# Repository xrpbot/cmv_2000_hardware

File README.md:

CMV2000 adapter kit
===================

This adapter kit allows connecting an [AMS CMV2000](https://ams.com/cmv2000)
image sensor to a ZedBoard (and probably other FPGA devboards) via the [FPGA
Mezzanine Card (FMC)](https://en.wikipedia.org/wiki/FPGA_Mezzanine_Card)
connector.

The CMV2000 is a high-speed image sensor intended for machine vision
applications (2 megapixels, 340 fps). While relatively expensive, it is one of
the few mid-range image sensors where reasonably complete documentation is
freely available (without NDA) from the manufacturer.

The hardware is split in two PCBs, connected by two high speed flat flex
cables. The first board contains the sensor, the second board connects to the
FMC port on the ZedBoard.

The sensor is powered by the ZedBoard, using the 12 V supply provided on the FMC
connector. Level shifters are used to translate all single-ended signals from
the FPGA I/O voltage to the 3.3 V used by the sensor.

The FMC board contains integrated 1k probes for some of the high-speed
differential signals. Additionally, a pin header allows probing the low-speed
single-ended signals.

For space reasons, the 1k probes use U.FL connectors for the connection to the
oscilloscope. The U.FL connectors have a very limited number of mating cycles
and the number of connections must therefore be kept to a minimum. Note that a
1k probe generally requires a termination (typically 50 Ω) at the oscilloscope;
with a high-impedance input, results will be very poor. If the 1k probes are
not required, the connectors and the corresponding resistors can simply be left
unpopulated.

See [pinmap.txt](pinmap.txt) for a list of connections from FPGA package pins
to camera pins.

Note that this repository uses submodules.

FMC board
---------

### Stackup

The FMC PCB is designed to be produced with 4 layers using the
[JLCPCB](https://jlcpcb.com/) JLC2313 stackup. (0.1 mm prepreg, ε<sub>r</sub> =
4.05 between the outer and inner layer.)

Using the JLCPCB impedance calculator, the following trace parameters were obtained:

100 Ω differential:
4.00 mil (102 µm) trace width / 5.00 mil (127 µm) space

50 Ω single-ended:
5.78 mil (147 µm) trace width

These results were cross-checked using Maarten Baerts [AlterPCB
TLineSim](https://www.maartenbaert.be/alterpcb/tlinesim/) tool. In addition,
the influence of ground pour on the signal layer was investigated (using the
"Coplanar Waveguide" geometry). A distance of >= 200 µm between the edge of the
signal trace and ground seems to have little effect on the impedance.

### Vias

JLC multilayer: min. via drill: 0.2 mm, min. via diameter: 0.45 mm

Known issues
------------

* Sensor board: The 3.0 V rail is generated with an LDO (U202) from the 3.3 V
rail. However, this drop is too low for the LDO to properly operate. On the
physical board, this is fixed with a bodge wire connecting the input of U202 to
the 5.0 V rail instead. However, this fix is not contained in the schematic or
layout.

* After the sensor board PCB was produced, we found out that the intended
31-pin connector (P102) was no longer available. Thus, a 41-pin connector had
to be bodged on (sacrificing the I2C EEPROM). This change is not documented in
the schematic. However, when the current version of the FMC board was designed,
it was adapted to the situation and uses a 41-pin connector. The end result is
that the boards, as found in this repository, are incompatible: the sensor
board uses a 51-pin and a 31-pin connector, while the FMC board uses a 51-pin
and a 41-pin connector.

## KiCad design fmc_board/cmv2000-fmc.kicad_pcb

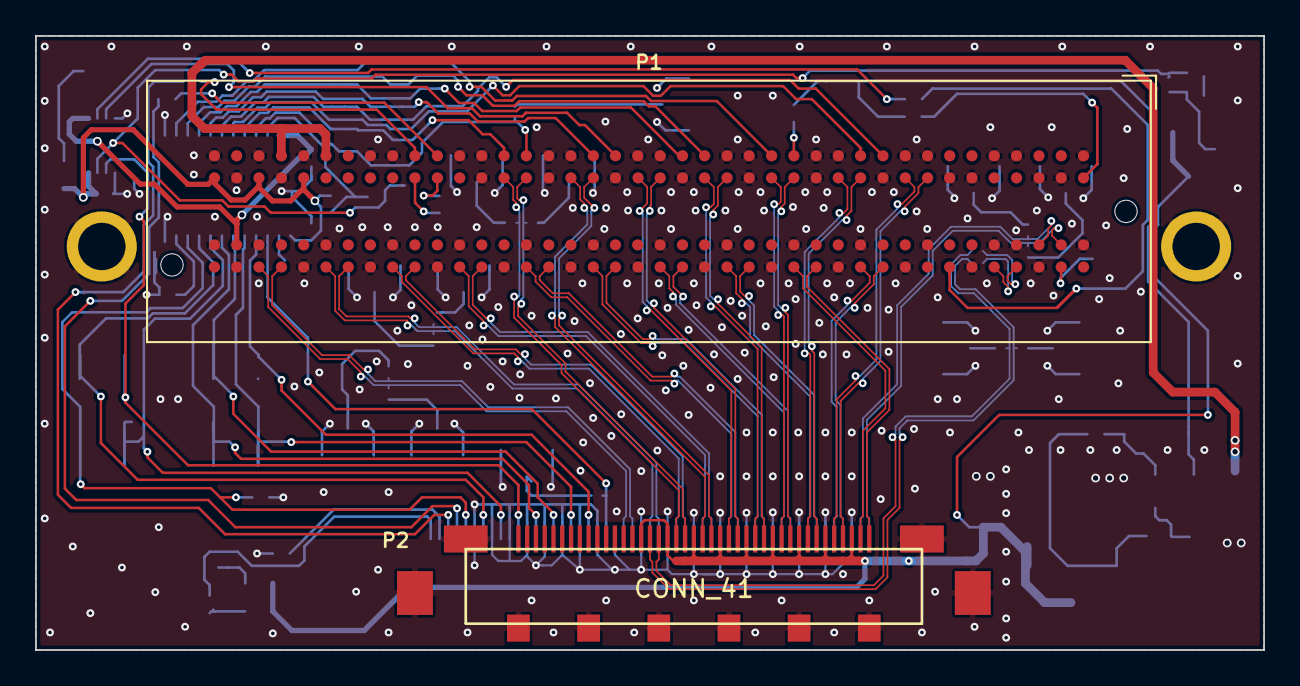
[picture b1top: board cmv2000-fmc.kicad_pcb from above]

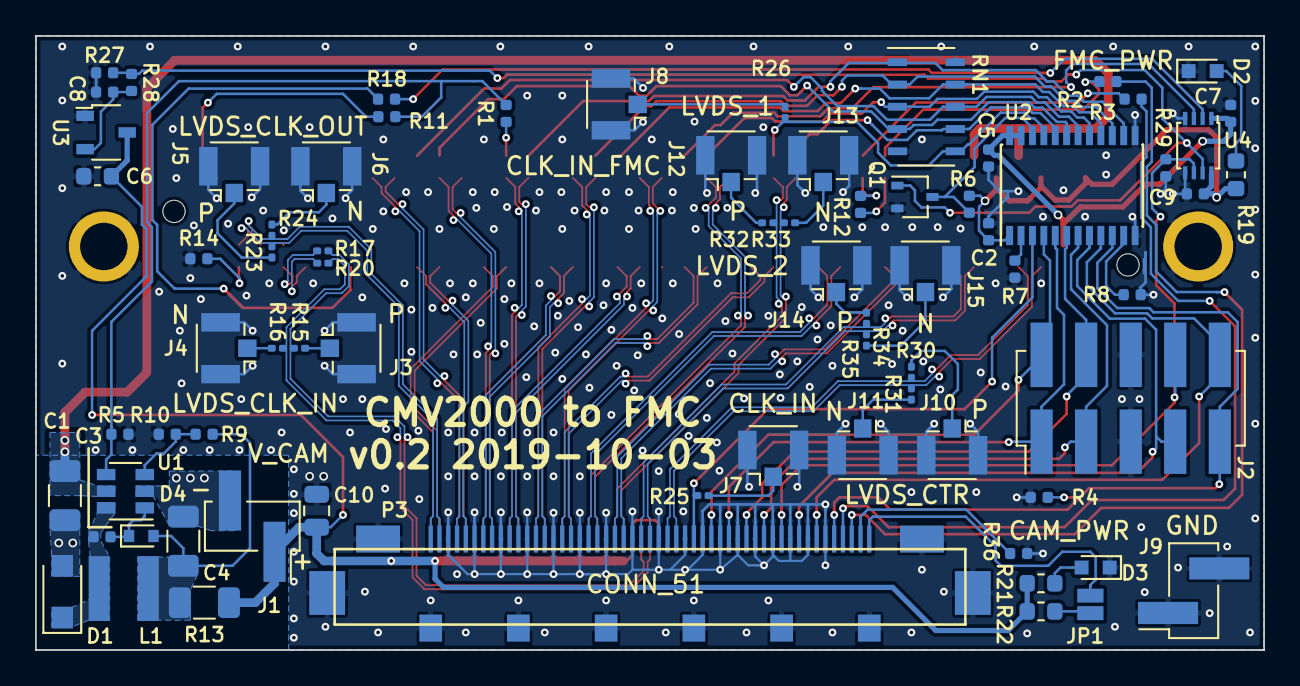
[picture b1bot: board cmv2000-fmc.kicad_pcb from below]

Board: 4 copper layers, 70.0 x 35.0 mm, 76 parts (74 on the bottom side), 101 nets.

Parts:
C1: 10uF, 25V; C_1206_3216Metric
C2, C5, C7, C9: 100n; C_0402_1005Metric
C3: 10n; C_0402_1005Metric
C4: 22uF, 10V; C_1206_3216Metric
C6: 1u; C_0603_1608Metric
C8: 1n; C_0402_1005Metric
C10: TBD; C_0805_2012Metric
D1: D; NRVTS245ESF
D2, D3: LED; 150060VS75000
D4: D; D_SOD-523
J1, J9: Conn_01x02; TSM-102-01-L-SV
J2: Conn_02x05; TSM-105-01-L-DV
J3: LVDS_CLK_IN_P; U.FL_Hirose_U.FL-R-SMT-1_Vertical
J4: LVDS_CLK_IN_N; U.FL_Hirose_U.FL-R-SMT-1_Vertical
J5: LVDS_CLK_OUT_P; U.FL_Hirose_U.FL-R-SMT-1_Vertical
J6: LVDS_CLK_OUT_N; U.FL_Hirose_U.FL-R-SMT-1_Vertical
J7, J8: CLK_IN; U.FL_Hirose_U.FL-R-SMT-1_Vertical
J10: LVDS_CTR_P; U.FL_Hirose_U.FL-R-SMT-1_Vertical
J11: LVDS_CTR_N; U.FL_Hirose_U.FL-R-SMT-1_Vertical
J12: LVDS_1_P; U.FL_Hirose_U.FL-R-SMT-1_Vertical
J13: LVDS_1_N; U.FL_Hirose_U.FL-R-SMT-1_Vertical
J14: LVDS_2_P; U.FL_Hirose_U.FL-R-SMT-1_Vertical
J15: LVDS_2_N; U.FL_Hirose_U.FL-R-SMT-1_Vertical
JP1: JUMPER; SOLDERSW_2
L1: 4.7uH; NRS4018
P1: FMC_LPC; Samtec_FMC_ASP-134604-01_4x40_Vertical
P2: CONN_41; FI-RE41S-HF-R1500
P3: CONN_51; FI-RE51S-HF-R1500
Q1: Q_NMOS_GSD; SOT-323_SC-70
R1, R2, R3, R36: DNP; R_0402_1005Metric
R4, R5, R6, R7, R8, R28: 10k; R_0402_1005Metric
R9: 49.9k; R_0402_1005Metric
R10: 9.53k; R_0402_1005Metric
R11, R12, R14, R18: 0; R_0402_1005Metric
R13: 0; R_1206_3216Metric
R15, R16, R23, R24, R25, R26, R30, R31, R32, R33, R34, R35: 1k; R_0201_0603Metric
R17, R20: DNP; R_0201_0603Metric
R19: 270R; R_0603_1608Metric
R21: 620R; R_0603_1608Metric
R22: TBD; R_0603_1608Metric
R27: 33k; R_0402_1005Metric
R29: 1M; R_0402_1005Metric
RN1: R_NET_BUS_8, 1M; EXB-A10P
U1: AP3211; SOT-23-6
U2: SN74AXC8T245; TSSOP-24_4.4x7.8mm_P0.65mm
U3: BD49xxx_GND1; SSOP3
U4: SN74LVC2T45; VSSOP-8_2.4x2.1mm_P0.5mm

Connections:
+3V3: C2.1, C9.1, P1.D36, P1.D38, P1.D40, R6.1, R19.1, U2.1, U4.8
+12V: C1.1, P1.C35, P1.C37, U1.5
/5V_CAM: C6.1, C10.1, J1.1, P2.15, P2.18, P2.21, P2.24, P2.27, P2.30, P2.33, P2.36, P2.39, R13.1, R21.1, R22.2, U3.3
/A0: P3.50, R36.2
/CAM_PWR_GOOD: Q1.1, R27.1, R28.1, U4.7
/CAM_PWR_GOOD_FMC: R18.1, U4.2
/CAM_PWR_ON: R1.2, R5.1, R11.1, U1.4
/CLK_IN: P3.31, R25.2, U2.3
/CLK_IN_FMC: P1.C26, R26.2, RN1.6, U2.21
/FRAME_REQ: J2.2, P3.33, U2.4
/FRAME_REQ_FMC: P1.C27, RN1.7, U2.20
/LED: JP1.2, P3.51
/LVDS_1_N: P1.D27, P2.19, R33.2
/LVDS_1_P: P1.D26, P2.20, R32.2
/LVDS_2_N: P1.H35, P3.26, R35.2
/LVDS_2_P: P1.H34, P3.25, R34.2
/LVDS_3_N: P1.H29, P3.20
/LVDS_3_P: P1.H28, P3.19
/LVDS_4_N: P1.H32, P3.23
/LVDS_4_P: P1.H31, P3.22
/LVDS_5_N: P1.D24, P2.22
/LVDS_5_P: P1.D23, P2.23
/LVDS_6_N: P1.D21, P2.25
/LVDS_6_P: P1.D20, P2.26
/LVDS_7_N: P1.H20, P3.11
/LVDS_7_P: P1.H19, P3.10
/LVDS_8_N: P1.H26, P3.17
/LVDS_8_P: P1.H25, P3.16
/LVDS_9_N: P1.H23, P3.14
/LVDS_9_P: P1.H22, P3.13
/LVDS_10_N: P1.H17, P3.8
/LVDS_10_P: P1.H16, P3.7
/LVDS_11_N: P1.D18, P2.28
/LVDS_11_P: P1.D17, P2.29
/LVDS_12_N: P1.D15, P2.31
/LVDS_12_P: P1.D14, P2.32
/LVDS_13_N: P1.H11, P3.5
/LVDS_13_P: P1.H10, P3.4
/LVDS_14_N: P1.D12, P2.34
/LVDS_14_P: P1.D11, P2.35
/LVDS_15_N: P1.H14, P2.40
/LVDS_15_P: P1.H13, P2.41
/LVDS_16_N: P1.D09, P2.37
/LVDS_16_P: P1.D08, P2.38
/LVDS_CLK_IN_0_N: P1.H05, R20.2
/LVDS_CLK_IN_0_P: P1.H04, R17.2
/LVDS_CLK_IN_N: P2.16, R16.2, R20.1
/LVDS_CLK_IN_P: P2.17, R15.2, R17.1
/LVDS_CLK_OUT_N: P1.G03, P3.2, R24.2
/LVDS_CLK_OUT_P: P1.G02, P3.1, R23.2
/LVDS_CTR_N: P1.H38, P3.29, R31.2
/LVDS_CTR_P: P1.H37, P3.28, R30.2
/SCL: P3.48, R3.2
/SDA: P3.49, R2.2
/SPI_CLK: J2.10, P3.45, U2.9
/SPI_CLK_FMC: P1.C18, RN1.2, U2.15
/SPI_EN: J2.7, P3.43, U2.8
/SPI_EN_FMC: P1.C19, RN1.9, U2.16
/SPI_IN: J2.3, P3.39, U2.7
/SPI_IN_FMC: P1.C23, RN1.3, U2.17
/SPI_OUT: J2.8, P3.41, R29.1, U4.6
/SPI_OUT_FMC: P1.C22, U4.3
/SYS_RES_N: J2.9, P3.47, R4.1, U2.10
/SYS_RES_N_FMC: P1.C15, RN1.1, U2.14
/T_EXP1: J2.4, P3.37, U2.6
/T_EXP1_FMC: P1.C10, RN1.8, U2.18
/T_EXP2: J2.1, P3.35, U2.5
/T_EXP2_FMC: P1.C11, RN1.4, U2.19
/VIO_FMC: C5.1, C7.1, P1.G39, U2.23, U2.24, U4.1
GND: C1.2, C2.2, C4.2, C5.2, C6.2, C7.2, C8.2, C9.2, C10.2, D1.2, D2.1, D3.1, J1.2, J2.5, J2.6, J3.2, J4.2, J5.2, J6.2, J7.2, J8.2, J9.1, J9.2, J10.2, J11.2, J12.2, J13.2, J14.2, J15.2, P1.C01, P1.C04, P1.C05, P1.C08, P1.C09, P1.C12, P1.C13, P1.C16, P1.C17, P1.C20, P1.C21, P1.C24, P1.C25, P1.C28, P1.C29, P1.C32, P1.C33, P1.C36, P1.C38, P1.C40, P1.D02, P1.D03, P1.D06, P1.D07, P1.D10, P1.D13, P1.D16, P1.D19, P1.D22, P1.D25, P1.D28, P1.D37, P1.D39, P1.G01, P1.G04, P1.G05, P1.G08, P1.G11, P1.G14, P1.G17, P1.G20, P1.G23, P1.G26, P1.G29, P1.G32, P1.G35, P1.G38, P1.G40, P1.H03, P1.H06, P1.H09, P1.H12, P1.H15, P1.H18, P1.H21, P1.H24, P1.H27, P1.H30, P1.H33, P1.H36, P1.H39, P2.SH, P3.3, P3.6, P3.9, P3.12, P3.15, P3.18, P3.21, P3.24, P3.27, P3.30, P3.32, P3.34, P3.36, P3.38, P3.40, P3.42, P3.44, P3.46, P3.SH, Q1.2, R4.2, R5.2, R7.2, R8.2, R10.2, R14.1, R27.2, R29.2, R36.1, RN1.5, RN1.10, U1.2, U2.12, U2.13, U3.1, U4.4, U4.5
unnamed: C3.1, D4.1, U1.1
unnamed: C3.2, D1.1, L1.1, U1.6
unnamed: C4.1, D4.2, L1.2, R9.1, R13.2
unnamed: C8.1, R28.2, U3.2
unnamed: D2.2, R19.2
unnamed: D3.2, R21.2
unnamed: J3.1, R15.1
unnamed: J4.1, R16.1
unnamed: J5.1, R23.1
unnamed: J6.1, R24.1
unnamed: J7.1, R25.1
unnamed: J8.1, R26.1
unnamed: J10.1, R30.1
unnamed: J11.1, R31.1
unnamed: J12.1, R32.1
unnamed: J13.1, R33.1
unnamed: J14.1, R34.1
unnamed: J15.1, R35.1
unnamed: JP1.1, R22.1
unnamed: P1.C14, R1.1
unnamed: P1.C30, R3.1
unnamed: P1.C31, R2.1
unnamed: P1.D01, R11.2
unnamed: P1.D30, R12.1
unnamed: P1.D31, R12.2
unnamed: P1.H02, R14.2
unnamed: P1.H07, R18.2
unnamed: Q1.3, R6.2, U2.22
unnamed: R7.1, U2.2
unnamed: R8.1, U2.11
unnamed: R9.2, R10.1, U1.3

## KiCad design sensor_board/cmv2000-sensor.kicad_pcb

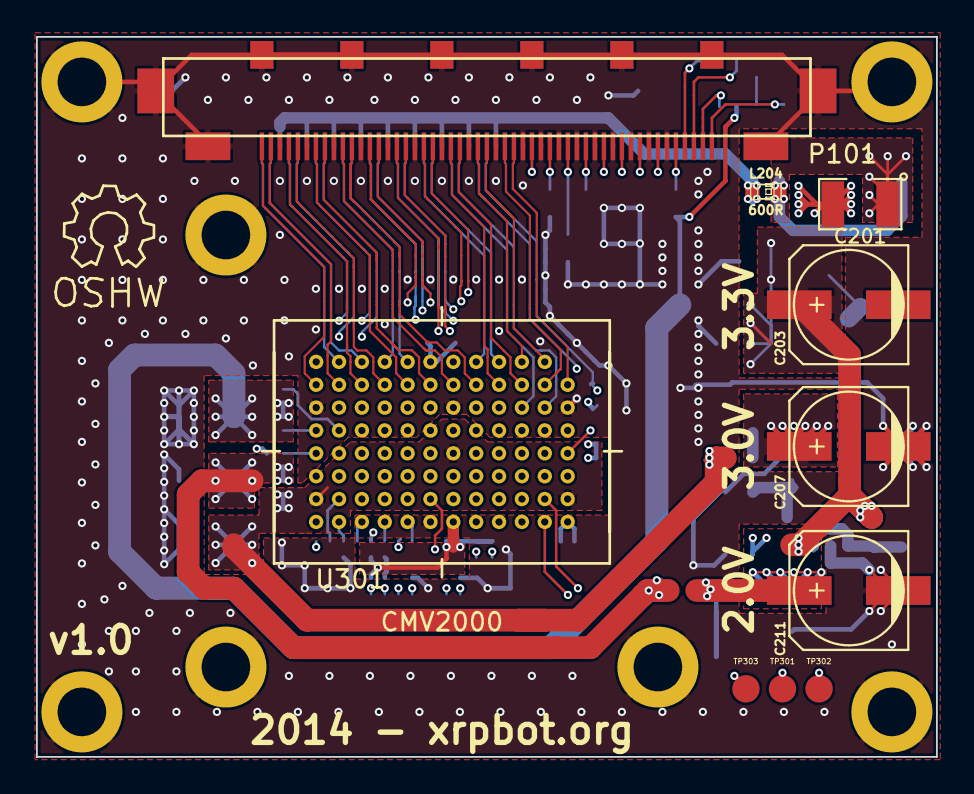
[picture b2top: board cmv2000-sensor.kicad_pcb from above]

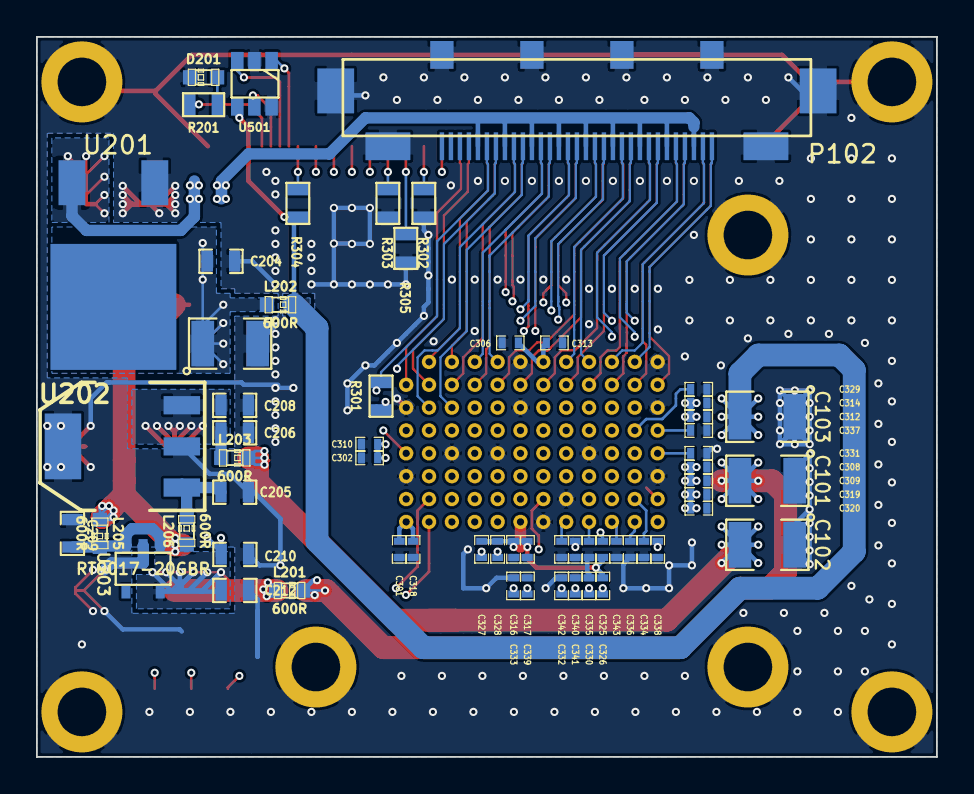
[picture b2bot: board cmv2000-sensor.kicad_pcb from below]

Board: 4 copper layers, 50.0 x 40.0 mm, 79 parts (61 on the bottom side), 85 nets.

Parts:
C101, C102, C103, C201, C202: 100µ; SM1210
C203, C207, C211: 330µ; c_elec_6.3x7.7
C204, C208, C212: 33µ; SM0603_Capa
C205, C206: 10µ; SM0603_Capa
C209, C210: 1µ; SM0603_Capa
C301, C309, C310, C313, C314, C317, C319: 4.7µ; SM0402_c
C302, C306, C308, C312, C316, C318, C320, C325, C326, C327, C328, C329, C330, C331, C332, C333, C334, C335, C336, C337, C338, C339, C340, C341, C342, C343: 100n; SM0402_c
D201: LED; LED-0603
L201, L202, L203, L204, L205, L206: 600R; LED-0603
P101: FI-RE51S-HF-R1500
P102: CONN_31; FI-RE31S-HF-R1500
R201: 680; SM0603
R301: 100; SM0603
R302, R303, R305: R; SM0603
R304: 10k; SM0603
SYM: Symbol_OSHW-Logo_SilkScreen_07Jul2012; Symbol_OSHW-Logo_SilkScreen
TP301, TP302, TP303: TESTPOINT; Measurement_Point_Round-SMD-Pad_Small
U201: AP1084; TO252-3
U202: MCP1826S; SOT223
U203: RT9017-20GBR; SOT23-5
U301: CMV2000
U401, U402, U403, U404, U405, U407, U408: MOUNTHOLE; MOUNTING_HOLE
U501: 24AA025E48; SOT23_6

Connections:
/CMV2000/2.0V: C101.2, C306.2, C308.2, C309.2, C313.2, L201.2, U301.A7, U301.C7, U301.E4, U301.E7, U301.E8
/CMV2000/3.0V: C102.2, C319.2, C320.2, L203.2, U301.E6, U301.G1, U301.G12
/CMV2000/3.3V: C103.2, C301.2, C302.2, C310.2, C312.2, C314.2, C316.2, C317.2, C318.2, C325.1, C326.1, C327.1, C328.1, L202.2, R304.1, U301.E2, U301.F7, U301.H1, U301.H6, U501.4
/CMV2000/CLK_IN: P101.21, U301.E1
/CMV2000/FRAME_REQ: P101.19, R302.1, U301.F2
/CMV2000/LVDS_1_N: P102.23, U301.C2
/CMV2000/LVDS_1_P: P102.22, U301.C3
/CMV2000/LVDS_2_N: P101.26, U301.A2
/CMV2000/LVDS_2_P: P101.27, U301.A3
/CMV2000/LVDS_3_N: P101.32, U301.D3
/CMV2000/LVDS_3_P: P101.33, U301.D4
/CMV2000/LVDS_4_N: P101.29, U301.B3
/CMV2000/LVDS_4_P: P101.30, U301.B4
/CMV2000/LVDS_5_N: P102.20, U301.A4
/CMV2000/LVDS_5_P: P102.19, U301.A5
/CMV2000/LVDS_6_N: P102.17, U301.C4
/CMV2000/LVDS_6_P: P102.16, U301.C5
/CMV2000/LVDS_7_N: P101.41, U301.B5
/CMV2000/LVDS_7_P: P101.42, U301.B6
/CMV2000/LVDS_8_N: P101.35, U301.D5
/CMV2000/LVDS_8_P: P101.36, U301.D6
/CMV2000/LVDS_9_N: P101.38, U301.D7
/CMV2000/LVDS_9_P: P101.39, U301.D8
/CMV2000/LVDS_10_N: P101.44, U301.B7
/CMV2000/LVDS_10_P: P101.45, U301.B8
/CMV2000/LVDS_11_N: P102.14, U301.C8
/CMV2000/LVDS_11_P: P102.13, U301.C9
/CMV2000/LVDS_12_N: P102.11, U301.A8
/CMV2000/LVDS_12_P: P102.10, U301.A9
/CMV2000/LVDS_13_N: P101.47, U301.B9
/CMV2000/LVDS_13_P: P101.48, U301.B10
/CMV2000/LVDS_14_N: P102.8, U301.D9
/CMV2000/LVDS_14_P: P102.7, U301.D10
/CMV2000/LVDS_15_N: P102.2, U301.A10
/CMV2000/LVDS_15_P: P102.1, U301.A11
/CMV2000/LVDS_16_N: P102.5, U301.C10
/CMV2000/LVDS_16_P: P102.4, U301.C11
/CMV2000/LVDS_CLK_IN_N: P102.26, R301.1, U301.D2
/CMV2000/LVDS_CLK_IN_P: P102.25, R301.2, U301.D1
/CMV2000/LVDS_CLK_OUT_N: P101.50, U301.B11
/CMV2000/LVDS_CLK_OUT_P: P101.51, U301.B12
/CMV2000/LVDS_CTR_N: P101.23, U301.B1
/CMV2000/LVDS_CTR_P: P101.24, U301.B2
/CMV2000/SPI_CLK: P101.7, U301.H4
/CMV2000/SPI_EN: P101.9, U301.G4
/CMV2000/SPI_IN: P101.13, U301.F3
/CMV2000/SPI_OUT: P101.11, U301.F4
/CMV2000/SYS_RES_N: P101.5, R304.2, U301.H5
/CMV2000/T_EXP1: P101.15, R303.1, U301.H3
/CMV2000/T_EXP2: P101.17, R305.1, U301.G3
/Power Supply/5V: L204.1, P102.3, P102.6, P102.9, P102.12, P102.15, P102.18, P102.21, P102.24, P102.27
/Power Supply/LED_3.3V: P101.1, R201.2
/Sheet53D8E0E2/A0: P101.2, U501.5
/Sheet53D8E0E2/SCL: P101.4, U501.1
/Sheet53D8E0E2/SDA: P101.3, U501.3
GND: C101.1, C102.1, C103.1, C201.2, C202.2, C203.2, C204.2, C205.2, C206.2, C207.2, C208.2, C209.2, C210.2, C211.2, C212.2, C301.1, C302.1, C306.1, C308.1, C309.1, C310.1, C312.1, C313.1, C314.1, C316.1, C317.1, C318.1, C319.1, C320.1, C329.1, C330.1, C331.1, C332.1, C333.1, C334.1, C335.1, C336.1, C337.1, C338.1, C339.1, C340.1, C341.1, C342.1, C343.1, D201.2, P101.6, P101.8, P101.10, P101.12, P101.14, P101.16, P101.18, P101.20, P101.22, P101.25, P101.28, P101.31, P101.34, P101.37, P101.40, P101.43, P101.46, P101.49, P101.52, P101.53, P101.54, P101.55, P101.56, P101.57, P101.58, P101.59, P101.60, P101.61, P102.32, P102.33, P102.34, P102.35, P102.36, P102.37, P102.38, P102.39, R302.2, R303.2, R305.2, U201.1, U202.2, U202.4, U203.2, U301.A6, U301.A12, U301.C1, U301.C6, U301.C12, U301.E3, U301.E5, U301.E9, U301.F1, U301.F12, U301.G8, U301.H7, U401.1, U402.1, U403.1, U404.1, U405.1, U407.1, U408.1, U501.2, U501.6
unnamed: C201.1, L204.2, U201.3
unnamed: C202.1, C203.1, C204.1, L202.1, L205.1, L206.1, U201.2
unnamed: C205.1, L206.2, U202.1
unnamed: C206.1, C207.1, C208.1, L203.1, U202.3
unnamed: C209.1, L205.2, U203.1, U203.3
unnamed: C210.1, C211.1, C212.1, L201.1, U203.5
unnamed: C325.2, U301.F10
unnamed: C326.2, U301.G10
unnamed: C327.2, U301.F5
unnamed: C328.2, U301.G5
unnamed: C329.2, U301.D11
unnamed: C330.2, U301.E10
unnamed: C331.2, U301.E12
unnamed: C332.2, U301.F8
unnamed: C333.2, U301.G6
unnamed: C334.2, U301.G11
unnamed: C335.2, U301.H9
unnamed: C336.2, U301.H11
unnamed: C337.2, U301.D12
unnamed: C338.2, U301.E11
unnamed: C339.2, U301.F6
unnamed: C340.2, U301.F9
unnamed: C341.2, U301.G9
unnamed: C342.2, U301.H8
unnamed: C343.2, U301.H10
unnamed: D201.1, R201.1
unnamed: TP301.1, U301.H2
unnamed: TP302.1, U301.G2
unnamed: TP303.1, U301.G7

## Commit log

2014-07-20 basic routing done
2014-07-20 v1.0
2014-07-20 remove now obsolete fmc lib
2014-07-20 fix some GND vias that were hanging in midair
2014-07-28 change 0.5mm pitch to 0.3mm pitch connector and add proper ground between all LVDS pairs.
2014-10-01 Increase via size
2014-12-08 rework connector design and differential routing
2014-12-08 add missing CONN_31
2014-12-08 add values to R302, R303, R305, minor cosmetic fixes, add vias to ground plane
2014-12-09 add OSHW logo, cleanup silkscreen
2014-12-25 add c-mount design files as they were manufactured
2019-06-01 original state (BUGGY, DO NOT USE)
2019-06-01 fixes for modern KiCad (v5) (BUGGY, DO NOT USE)
2019-07-05 fix mirrored JAE connectors (P2 and P3), correct signal names
2019-07-05 add .gitignore
2019-07-05 fixes for modern KiCad (v5)
2019-07-05 move project-specific schematic symbols to symbols/ subdirectory
2019-09-23 major updates to schematic
    * add DC/DC converter to generate camera supply from 12V provided by FMC
    * enable camera supply only after FPGA supply is up
    * report camera supply status to FPGA
    * add level shifters for all single-ended signals
    * enable single-ended signals to camera only after camera supply is up
    * make sure single-ended signals to camera have well-defined value while
2019-09-23 add 3d models for Samtec TSM pin headers
2019-09-23 work on layout, change high-frequency resistors to 0201
2019-09-23 slightly increase spacing between pin headers J2 and J9
2019-09-23 update Samtec FMC ASP-134604-01 connector
2019-09-23 replace custom Hirose U.FL-R-SMT-1 footprint by upstream one
2019-09-23 first version of layout (still WIP)
2019-09-23 use thermal relief on back side (except for U.FL connectors)
2019-09-23 tweaking
2019-09-30 fix incorrect pin names in FMC LPC symbol
    Unfortunately, KiCad re-ordered the pins in the file when saving, so the real diff is below:
    * pin C03: DP0_C2M_P -> DP0_C2M_N
    * pin D35: GA0 -> GA1
2019-09-30 use R27 and R28 as voltage divider at voltage detector (U3) output
2019-09-30 add optional bootstrap diode, as recommended by AP3211 appnote
2019-09-30 fix two courtyard DRC problems
2019-10-02 fix settings for zones on inner layers
2019-10-02 more tweaking, change export settings
2020-12-23 move sensor board into subdirectory
2020-12-23 move FMC board into subdirectory
2020-12-24 add README
